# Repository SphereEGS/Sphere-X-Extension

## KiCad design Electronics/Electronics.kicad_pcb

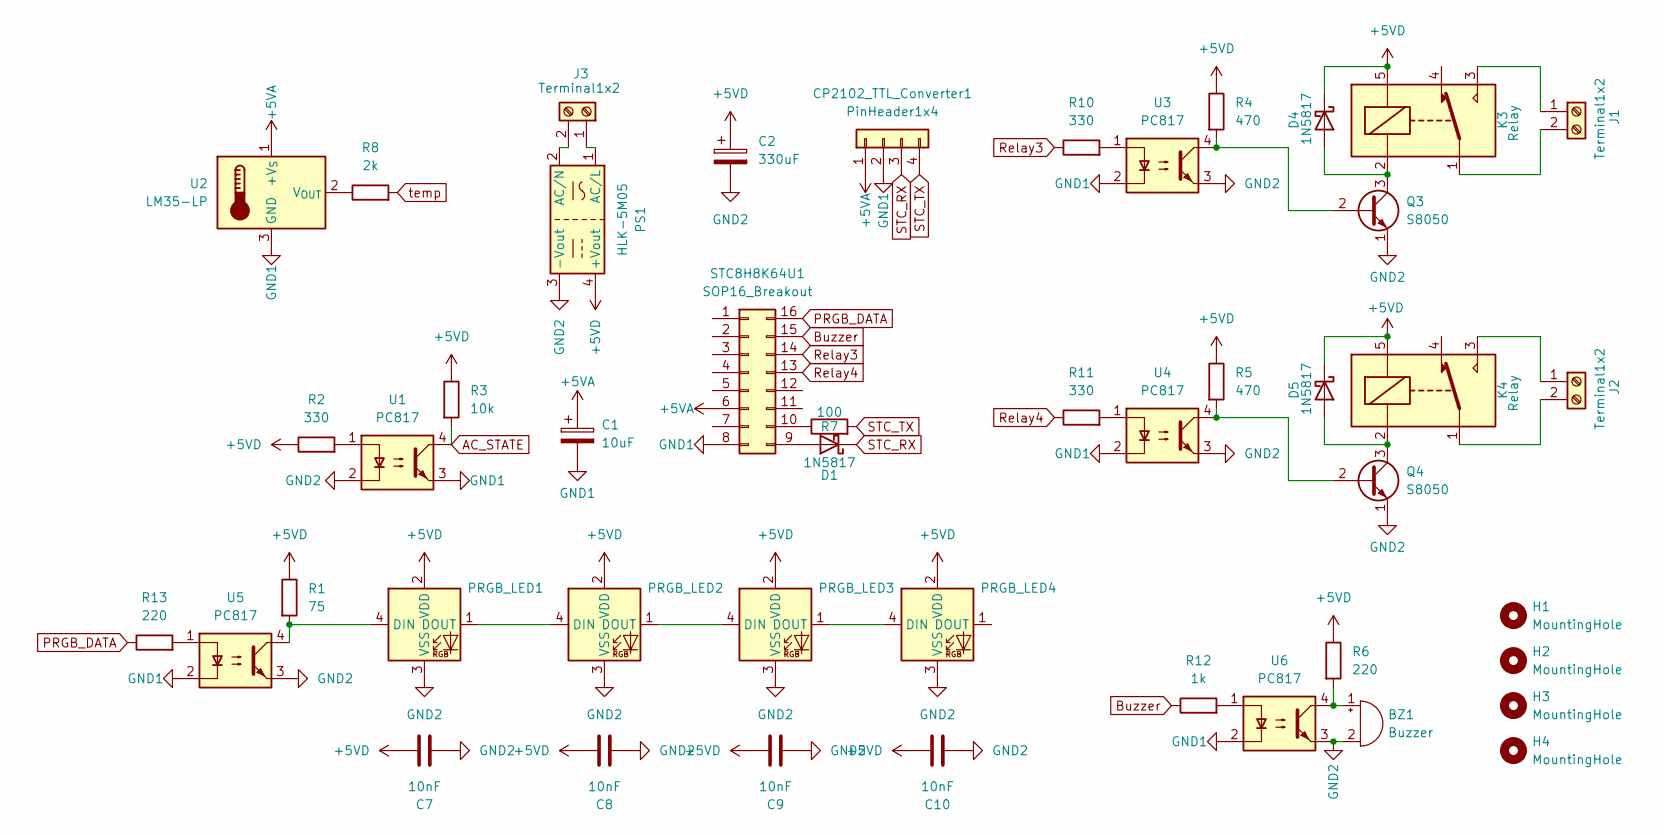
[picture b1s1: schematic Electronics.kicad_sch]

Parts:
BZ1: Buzzer; Buzzer_TDK_PS1240P02BT_D12.2mm_H6.5mm
C1: 10uF; CP_Radial_D5.0mm_P2.50mm
C2: 330uF; CP_Radial_D6.3mm_P2.50mm
C7, C8, C9, C10: 10nF; C_Disc_D5.0mm_W2.5mm_P2.50mm
CP2102_TTL_Converter1: PinHeader1x4; PinSocket_1x04_P2.54mm_Vertical
D1, D4, D5: 1N5817; D_DO-41_SOD81_P7.62mm_Horizontal
H1, H2, H3, H4: MountingHole; MountingHole_2.7mm_Pad
J1, J2, J3: Terminal1x2; TerminalBlock_bornier-2_P5.08mm
K3, K4: Relay; Relay_SPDT_SANYOU_SRD_Series_Form_C
PRGB_LED1, PRGB_LED2, PRGB_LED3, PRGB_LED4: PRGB_LED_DIP_Wide
PS1: HLK-5M05; Converter_ACDC_Hi-Link_HLK-5Mxx
Q3, Q4: S8050; TO-92_Inline_Wide
R1: 75; R_Axial_DIN0207_L6.3mm_D2.5mm_P7.62mm_Horizontal
R2, R10, R11: 330; R_Axial_DIN0207_L6.3mm_D2.5mm_P7.62mm_Horizontal
R3: 10k; R_Axial_DIN0207_L6.3mm_D2.5mm_P7.62mm_Horizontal
R4, R5: 470; R_Axial_DIN0207_L6.3mm_D2.5mm_P7.62mm_Horizontal
R6, R13: 220; R_Axial_DIN0207_L6.3mm_D2.5mm_P7.62mm_Horizontal
R7: 100; R_Axial_DIN0207_L6.3mm_D2.5mm_P7.62mm_Horizontal
R8: 2k; R_Axial_DIN0207_L6.3mm_D2.5mm_P7.62mm_Horizontal
R12: 1k; R_Axial_DIN0207_L6.3mm_D2.5mm_P7.62mm_Horizontal
STC8H8K64U1: SOP16_Breakout; Pololu_Breakout-16_15.2x20.3mm
U1, U3, U4, U5, U6: PC817; DIP-4_W7.62mm
U2: LM35-LP; TO-92L_Inline_Wide

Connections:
+5VA: C1.1, CP2102_TTL_Converter1.1, STC8H8K64U1.6, U2.1 (+V_{S})
+5VD: C2.1, C7.2, C8.2, C9.2, C10.2, D4.1 (K), D5.1 (K), K3.5, K4.5, PRGB_LED1.2 (VDD), PRGB_LED2.2 (VDD), PRGB_LED3.2 (VDD), PRGB_LED4.2 (VDD), PS1.4 (+Vout), R1.1, R2.1, R3.1, R4.1, R5.1, R6.1
AC_STATE: R3.2, U1.4
Buzzer: R12.1, STC8H8K64U1.15
GND1: C1.2, CP2102_TTL_Converter1.2, STC8H8K64U1.8, U1.3, U2.3 (GND), U3.2, U4.2, U5.2, U6.2
GND2: BZ1.2 (-), C2.2, C7.1, C8.1, C9.1, C10.1, PRGB_LED1.3 (VSS), PRGB_LED2.3 (VSS), PRGB_LED3.3 (VSS), PRGB_LED4.3 (VSS), PS1.3 (-Vout), Q3.1 (E), Q4.1 (E), U1.2, U3.3, U4.3, U5.3, U6.3
unnamed: BZ1.1 (+), R6.2, U6.4
unnamed: D1.2 (A), STC8H8K64U1.9
unnamed: D4.2 (A), K3.2, Q3.3 (C)
unnamed: D5.2 (A), K4.2, Q4.3 (C)
unnamed: J1.1, K3.3
unnamed: J1.2, K3.1
unnamed: J2.1, K4.3
unnamed: J2.2, K4.1
unnamed: J3.1, PS1.1 (AC/L)
unnamed: J3.2, PS1.2 (AC/N)
unnamed: PRGB_LED1.4 (DIN), R1.2, U5.4
unnamed: PRGB_LED1.1 (DOUT), PRGB_LED2.4 (DIN)
unnamed: PRGB_LED2.1 (DOUT), PRGB_LED3.4 (DIN)
unnamed: PRGB_LED3.1 (DOUT), PRGB_LED4.4 (DIN)
unnamed: Q3.2 (B), R4.2, U3.4
unnamed: Q4.2 (B), R5.2, U4.4
unnamed: R2.2, U1.1
unnamed: R10.2, U3.1
unnamed: R11.2, U4.1
unnamed: R12.2, U6.1
unnamed: R13.2, U5.1
unnamed: R7.1, STC8H8K64U1.10
unnamed: R8.1, U2.2 (V_{OUT})
PRGB_DATA: R13.1, STC8H8K64U1.16
Relay3: R10.1, STC8H8K64U1.14
Relay4: R11.1, STC8H8K64U1.13
STC_RX: CP2102_TTL_Converter1.3, D1.1 (K)
STC_TX: CP2102_TTL_Converter1.4, R7.2
temp: R8.2

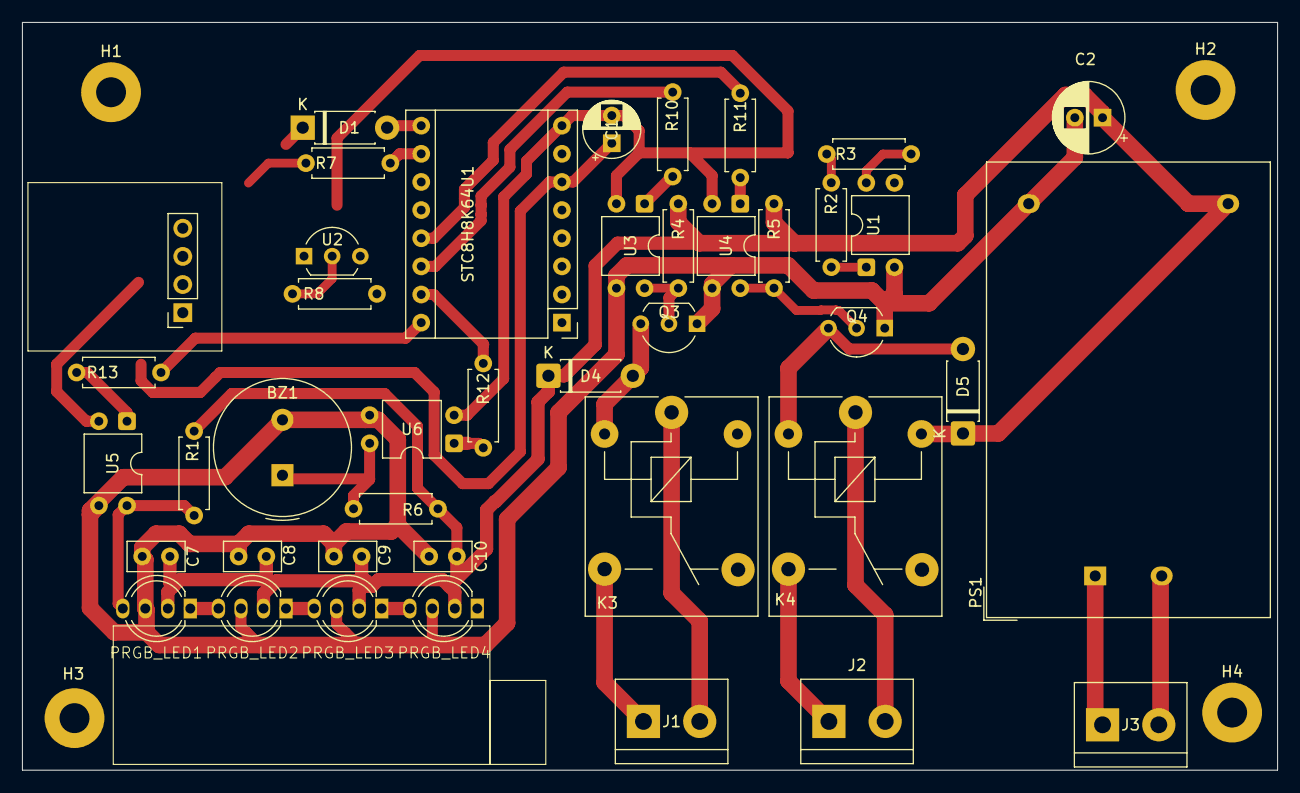
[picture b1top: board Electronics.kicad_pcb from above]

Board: 2 copper layers, 113.3 x 67.5 mm, 46 parts (0 on the bottom side), 34 nets.

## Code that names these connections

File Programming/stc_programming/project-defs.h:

#ifndef PROJECT_DEFS_H
#define PROJECT_DEFS_H

/* gpio-hal Settings */
#define WS2812_DATA_PORT 3
#define WS2812_DATA_PIN 7
#define BUZZER_PORT 3
#define BUZZER_PIN 6
#define RELAY1_PORT 3
#define RELAY1_PIN 5
#define RELAY2_PORT 3
#define RELAY2_PIN 4
#define RELAY3_PORT 3
#define RELAY3_PIN 3
#define RELAY4_PORT 3
#define RELAY4_PIN 2

/* uart-hal Settings */
#define CONSOLE_SPEED 115200
#define CONSOLE_UART UART1
#define CONSOLE_PIN_CONFIG 0  // TX->P3.1, RX->P3.0

/* timer-hal configs */
#define GLOBAL_TIMER TIMER0
#define GLOBAL_TIMER_ISR timer0_isr
#define GLOBAL_TIMER_INTERRUPT TIMER0_INTERRUPT

// Others 
#define LED_BLINK_PERIOD 400

#include <STC/8G1Kxx/TSSOP20.h>
#include <stdio.h>
#include <stdint.h>
#include <delay.h>
#include <gpio-hal.h>
#include <uart-hal.h>
#include <serial-console.h>
#include <timer-hal.h>
#include "global_timer.h"
#include "ws2812d.h"
#include "buzzer.h"
#include "relays.h"
#include "terminal.h"
#include "protocol.h"


#endif

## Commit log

2025-04-30 added initial schematics
2025-04-30 finished STC Microcontroller Code structure and most init functions
2025-05-01 finished circuit schematic, pin assignment, added inits of ws2812 PRGB LED
2025-05-02 finished C implementation of Relay Control
2025-05-03 finished PCB layout
2025-05-03 added Toggle functionality using real-time control on STC microcontroller
2025-05-03 Finished Python API
2025-05-03 added a force anchor hole for the PCB
2025-05-03 started 3D modelling enclosure
2025-05-04 updated pin assignments
2025-05-04 added mapping for new relays
2025-05-08 added schematic and PCB layout for mechanical relays
2025-05-08 added temperature sensor and AC detect schematic and PCB layout
